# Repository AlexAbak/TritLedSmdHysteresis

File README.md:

# TritLedSmdHysteresis
Индикатор трита с гистерезисом

Документация и обсуждение https://myweek-end.ru/trit/tritledhysteresis

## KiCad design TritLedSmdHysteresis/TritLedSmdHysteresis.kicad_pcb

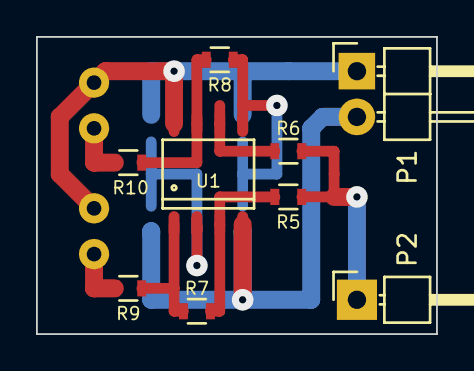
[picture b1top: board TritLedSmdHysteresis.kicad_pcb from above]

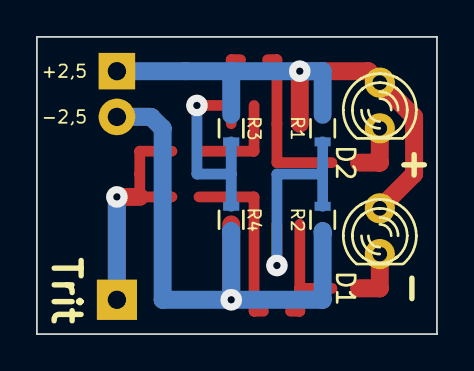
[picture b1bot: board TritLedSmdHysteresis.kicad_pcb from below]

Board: 2 copper layers, 22.2 x 16.5 mm, 15 parts (6 on the bottom side), 11 nets.

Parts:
D1: -; LED-3MM
D2: +; LED-3MM
P1: Power; Pin_Header_Angled_1x02
P2: In; Pin_Header_Angled_1x01
R1: 5,6Ω; R_0603
R2: 10КΩ; R_0603
R3: 22КΩ; R_0603
R4: 5,1КΩ; R_0603
R5, R6, R8: 4,7КΩ; R_0603
R7: 15КΩ; R_0603
R9, R10: 220Ω; R_0603
U1: LM393; SO-8

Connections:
unnamed: D1.1, D2.1, P1.1, R1.1, R3.1, U1.8
unnamed: D1.2, R9.1
unnamed: D2.2, R10.1
unnamed: P1.2, R2.2, R4.2, U1.4
unnamed: P2.1, R5.2, R6.2
unnamed: R1.2, R2.1, U1.2
unnamed: R3.2, R4.1, R8.2, U1.5
unnamed: R5.1, R7.2, U1.3
unnamed: R6.1, U1.6
unnamed: R7.1, R9.2, U1.1
unnamed: R8.1, R10.2, U1.7

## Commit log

2015-04-27 Заливка схемы
2015-04-27 Косметические процедуры
2015-04-28 Расчёт сопротивлений
